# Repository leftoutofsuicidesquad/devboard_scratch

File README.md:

# devboard_scratch
Devboard from Scratch

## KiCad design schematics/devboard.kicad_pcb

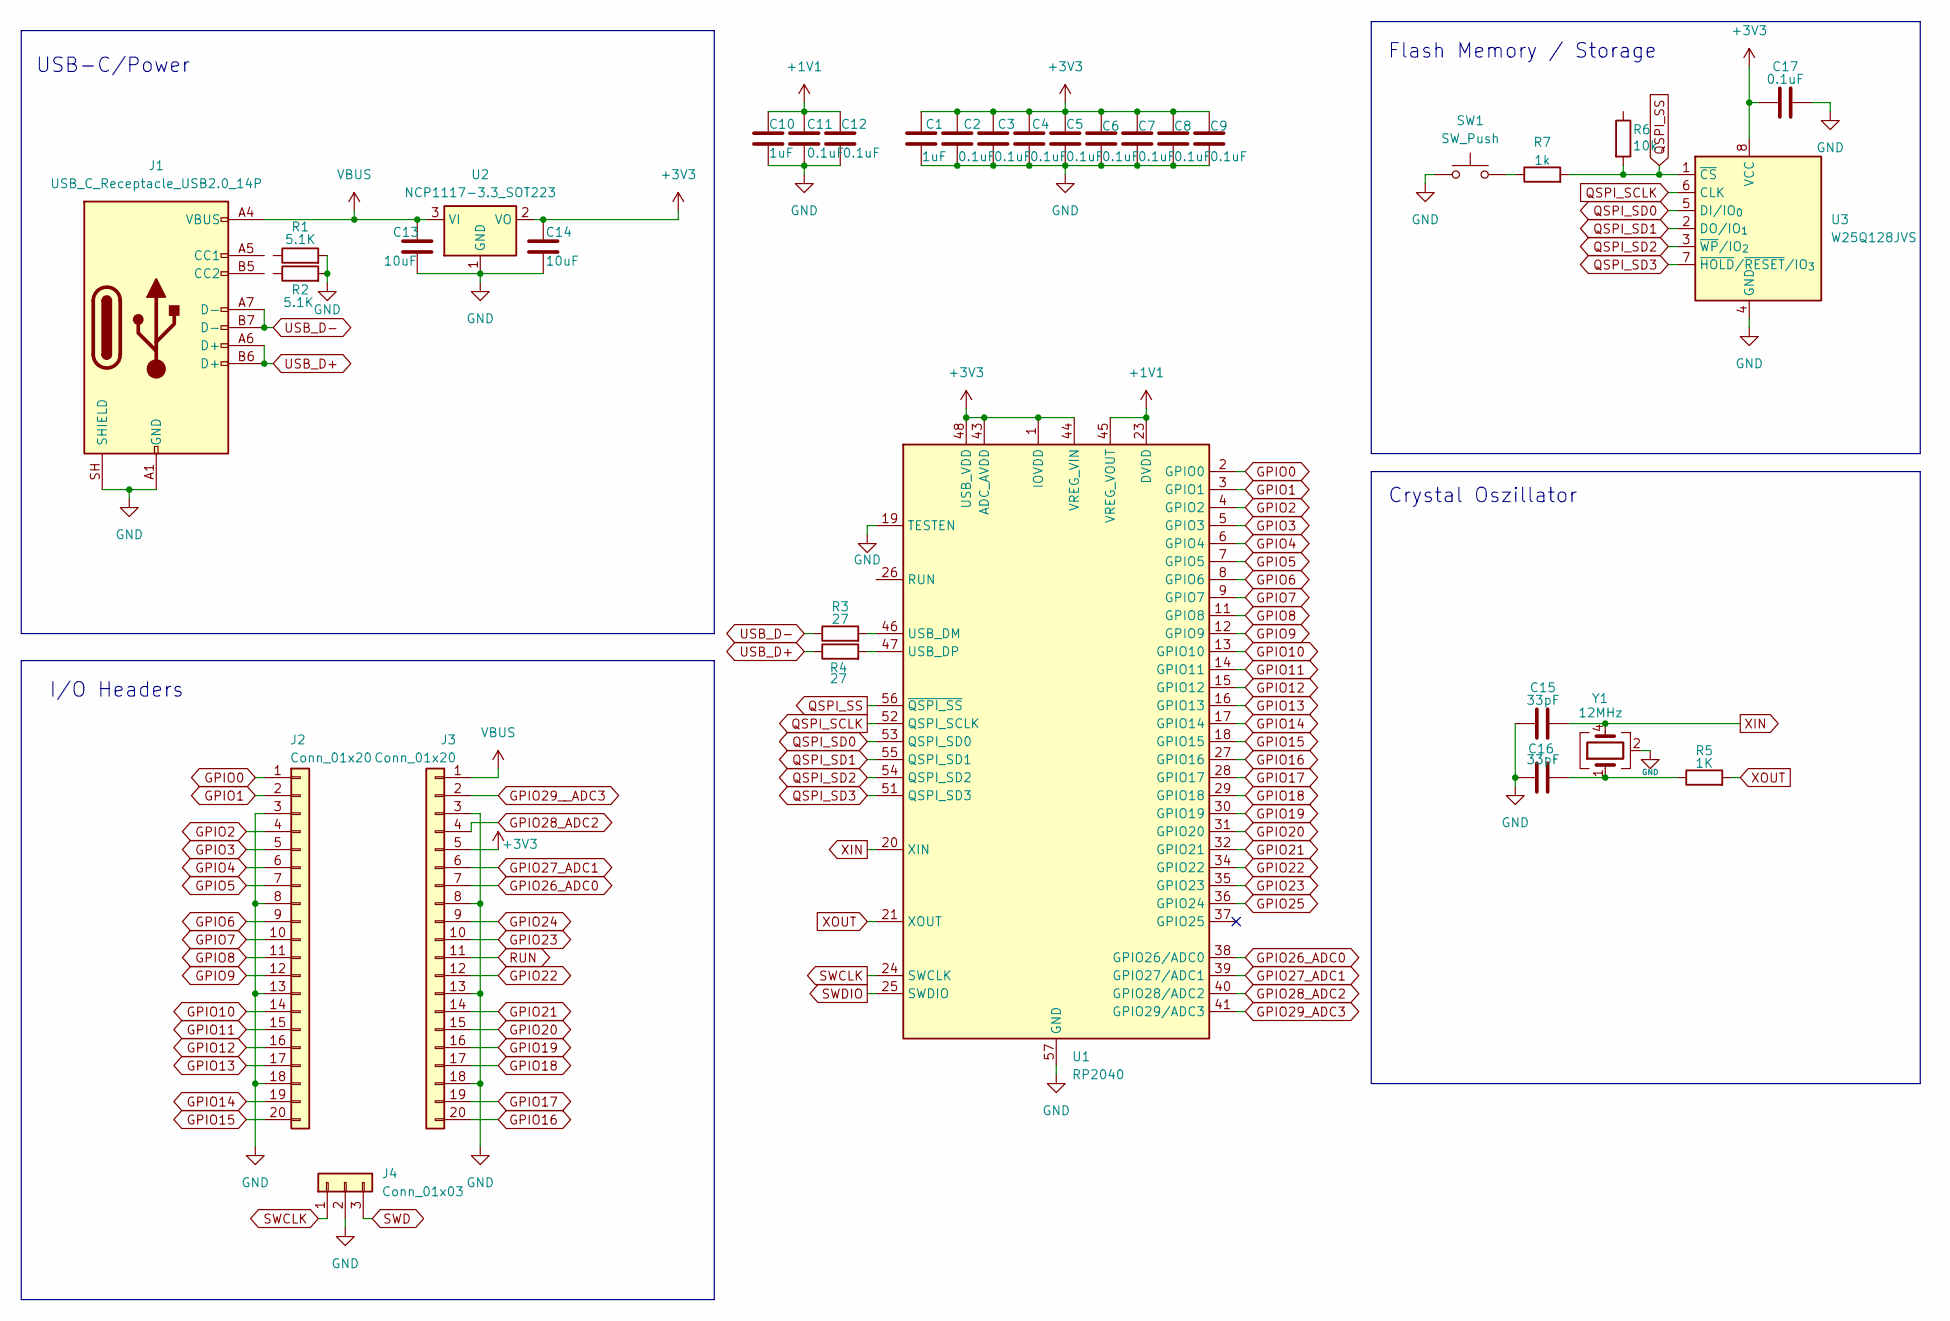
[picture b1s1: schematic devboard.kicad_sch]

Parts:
C1, C10: 1uF; C_0402_1005Metric
C2, C3, C4, C5, C6, C7, C8, C9, C11, C12, C17: 0.1uF; C_0402_1005Metric
C13, C14: 10uF; C_0201_0603Metric
C15, C16: 33pF; C_0402_1005Metric
J1: USB_C_Receptacle_USB2.0_14P; USB_C_Receptacle_HRO_TYPE-C-31-M-12
J2, J3: Conn_01x20; PinHeader_1x20_P2.54mm_Vertical
J4: Conn_01x03; PinHeader_1x03_P2.54mm_Vertical
R1, R2: 5.1K; R_0402_1005Metric
R3, R4: 27; R_0402_1005Metric
R5: 1K; R_0402_1005Metric
R6: 10k; R_0402_1005Metric
R7: 1k; R_0402_1005Metric
SW1: SW_Push; SW_Push_SPST_NO_Alps_SKRK
U1: RP2040; QFN-56-1EP_7x7mm_P0.4mm_EP3.2x3.2mm
U2: NCP1117-3.3_SOT223; SOT-223-3_TabPin2
U3: W25Q128JVS; SOIC-8_5.3x5.3mm_P1.27mm
Y1: 12MHz; Crystal_SMD_3225-4Pin_3.2x2.5mm

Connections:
+1V1: C10.1, C11.1, C12.1, U1.23 (DVDD), U1.45 (VREG_VOUT), U1.50 (DVDD)
+3V3: C1.1, C2.1, C3.1, C4.1, C5.1, C6.1, C7.1, C8.1, C9.1, C14.1, C17.1, J3.5, U1.1 (IOVDD), U1.10 (IOVDD), U1.22 (IOVDD), U1.33 (IOVDD), U1.42 (IOVDD), U1.43 (ADC_AVDD), U1.44 (VREG_VIN), U1.48 (USB_VDD), U1.49 (IOVDD), U2.2 (VO), U3.8 (VCC)
GND: C1.2, C2.2, C3.2, C4.2, C5.2, C6.2, C7.2, C8.2, C9.2, C10.2, C11.2, C12.2, C13.2, C14.2, C15.1, C16.1, C17.2, J1.A1 (GND), J1.A12 (GND), J1.B1 (GND), J1.B12 (GND), J1.SH (SHIELD), J2.3, J2.8, J2.13, J2.18, J3.3, J3.8, J3.13, J3.18, J4.2, R1.2, R2.2, SW1.1, U1.19 (TESTEN), U1.57 (GND), U2.1 (GND), U3.4 (GND), Y1.2 (G), Y1.3 (G)
GPIO0: J2.1, U1.2 (GPIO0)
GPIO1: J2.2, U1.3 (GPIO1)
GPIO2: J2.4, U1.4 (GPIO2)
GPIO3: J2.5, U1.5 (GPIO3)
GPIO4: J2.6, U1.6 (GPIO4)
GPIO5: J2.7, U1.7 (GPIO5)
GPIO6: J2.9, U1.8 (GPIO6)
GPIO7: J2.10, U1.9 (GPIO7)
GPIO8: J2.11, U1.11 (GPIO8)
GPIO9: J2.12, U1.12 (GPIO9)
GPIO10: J2.14, U1.13 (GPIO10)
GPIO11: J2.15, U1.14 (GPIO11)
GPIO12: J2.16, U1.15 (GPIO12)
GPIO13: J2.17, U1.16 (GPIO13)
GPIO14: J2.19, U1.17 (GPIO14)
GPIO15: J2.20, U1.18 (GPIO15)
GPIO16: J3.20, U1.27 (GPIO16)
GPIO17: J3.19, U1.28 (GPIO17)
GPIO18: J3.17, U1.29 (GPIO18)
GPIO19: J3.16, U1.30 (GPIO19)
GPIO20: J3.15, U1.31 (GPIO20)
GPIO21: J3.14, U1.32 (GPIO21)
GPIO22: J3.12, U1.34 (GPIO22)
GPIO23: J3.10, U1.35 (GPIO23)
GPIO24: J3.9
GPIO25: U1.36 (GPIO24)
GPIO26_ADC0: J3.7, U1.38 (GPIO26/ADC0)
GPIO27_ADC1: J3.6, U1.39 (GPIO27/ADC1)
GPIO28_ADC2: J3.4, U1.40 (GPIO28/ADC2)
GPIO29_ADC3: U1.41 (GPIO29/ADC3)
GPIO29__ADC3: J3.2
unnamed: C16.2, R5.1, Y1.1
unnamed: R7.1, SW1.2
unnamed: R3.2, U1.46 (USB_DM)
unnamed: R4.2, U1.47 (USB_DP)
QSPI_SCLK: U1.52 (QSPI_SCLK), U3.6 (CLK)
QSPI_SD0: U1.53 (QSPI_SD0), U3.5 (DI/IO_{0})
QSPI_SD1: U1.55 (QSPI_SD1), U3.2 (DO/IO_{1})
QSPI_SD2: U1.54 (QSPI_SD2), U3.3 (~WP/IO_{2})
QSPI_SD3: U1.51 (QSPI_SD3), U3.7 (~HOLD/~RESET/IO_{3})
QSPI_SS: R6.2, R7.2, U1.56 (~QSPI_SS), U3.1 (~CS)
RUN: J3.11
SWCLK: J4.1, U1.24 (SWCLK)
SWD: J4.3
SWDIO: U1.25 (SWDIO)
USB_D+: J1.A6 (D+), J1.B6 (D+), R4.1
USB_D-: J1.A7 (D-), J1.B7 (D-), R3.1
VBUS: C13.1, J1.A4 (VBUS), J1.A9 (VBUS), J1.B4 (VBUS), J1.B9 (VBUS), J3.1, U2.3 (VI)
XIN: C15.2, U1.20 (XIN), Y1.4
XOUT: R5.2, U1.21 (XOUT)

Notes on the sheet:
I/O Headers
Flash Memory / Storage
USB-C/Power
Crystal Oszillator

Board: 2 copper layers, 33 parts (0 on the bottom side), 46 nets, no tracks yet.
